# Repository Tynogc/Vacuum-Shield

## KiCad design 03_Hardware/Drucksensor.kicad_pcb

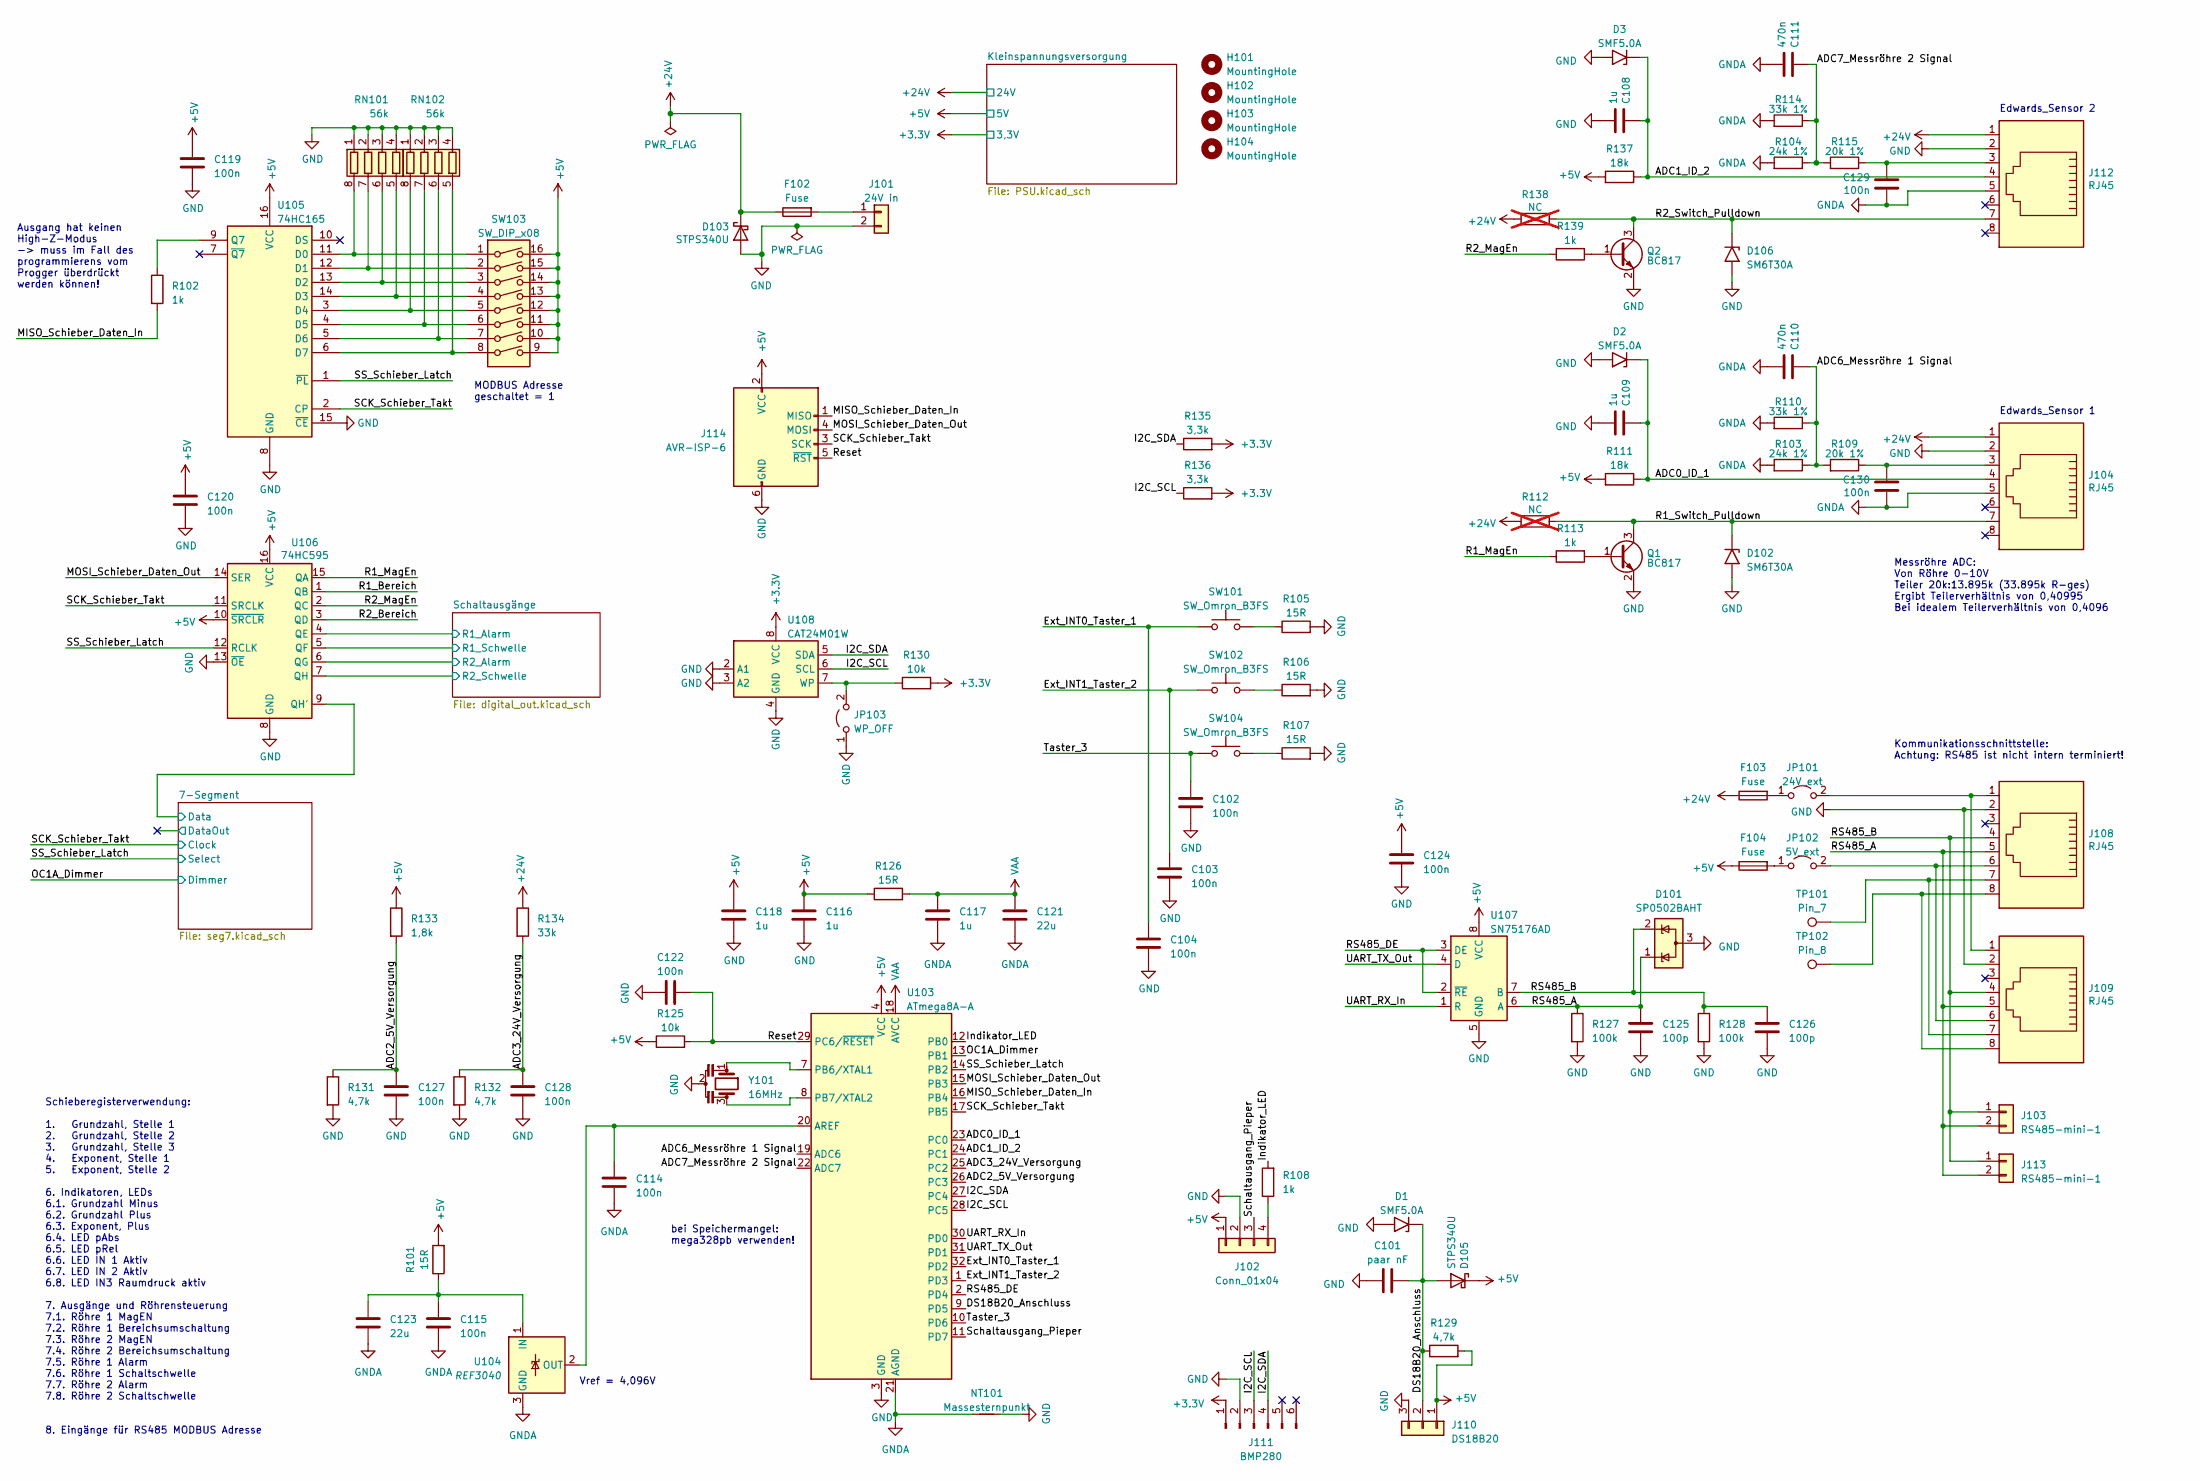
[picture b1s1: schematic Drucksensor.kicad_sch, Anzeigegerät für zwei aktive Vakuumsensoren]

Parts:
C101: paar nF; C_0603_1608Metric
C102, C103, C104, C114, C115, C119, C120, C122, C124, C127, C128, C129, C130: 100n; C_0603_1608Metric
C108, C109, C116, C117, C118: 1u; C_0603_1608Metric
C110, C111: 470n; C_0603_1608Metric
C121, C123: 22u; C_1206_3216Metric
C125, C126: 100p; C_0603_1608Metric
D1, D2, D3: SMF5.0A; D_SOD-123F
D101: SP0502BAHT; SOT-23
D102, D106: SM6T30A; D_SMB
D103, D105: STPS340U; D_SMB
F102, F103, F104: Fuse; R_1210_3225Metric
H101, H102, H103, H104: MountingHole; MountingHole_3.2mm_M3_DIN965
J101: 24V in; JST_XH_B2B-XH-A_1x02_P2.50mm_Vertical
J102: Conn_01x04; PinHeader_2x02_P2.54mm_Vertical
J103, J113: RS485-mini-1; JST_XH_B2B-XH-AM_1x02_P2.50mm_Vertical
J104, J108, J109, J112: RJ45; RJ45_Amphenol_54602_mod
J110: DS18B20; JST_XH_B3B-XH-AM_1x03_P2.50mm_Vertical
J111: BMP280; PinHeader_1x06_P2.54mm_Vertical
J114: AVR-ISP-6; IDC-Header_2x03_P2.54mm_Vertical
JP101: 24V_ext; PinHeader_1x02_P2.54mm_Vertical
JP102: 5V_ext; PinHeader_1x02_P2.54mm_Vertical
JP103: WP_OFF; PinHeader_1x02_P2.54mm_Vertical
NT101: Massesternpunkt; NetTie-2_SMD_Pad0.5mm
Q1, Q2: BC817; SOT-23
R101, R126: 15R; R_1206_3216Metric
R102, R108, R113, R139: 1k; R_0603_1608Metric
R103, R104: 24k 1%; R_0603_1608Metric
R105, R106, R107: 15R; R_0603_1608Metric
R109, R115: 20k 1%; R_0603_1608Metric
R110, R114: 33k 1%; R_0603_1608Metric
R111, R137: 18k; R_0603_1608Metric
R112, R138: NC; R_1206_3216Metric; not fitted
R125, R130: 10k; R_0603_1608Metric
R127, R128: 100k; R_0603_1608Metric
R129, R131, R132: 4,7k; R_0603_1608Metric
R133: 1,8k; R_0603_1608Metric
R134: 33k; R_0603_1608Metric
R135, R136: 3,3k; R_0603_1608Metric
RN101, RN102: 56k; R_Array_Convex_4x1206; Digikey YC164J-56KCT-ND
SW101, SW102, SW104: SW_Omron_B3FS; SW_PUSH-12mm
SW103: SW_DIP_x08; SW_DIP_SPSTx08_Slide_9.78x22.5mm_W7.62mm_P2.54mm
TP101: Pin_7; TestPoint_Keystone_5005-5009_Compact
TP102: Pin_8; TestPoint_Keystone_5005-5009_Compact
U103: ATmega8A-A; TQFP-32_7x7mm_P0.8mm
U104: REF3040; SOT-23
U105: 74HC165; SOIC-16_3.9x9.9mm_P1.27mm
U106: 74HC595; SOIC-16_3.9x9.9mm_P1.27mm
U107: SN75176AD; SOIC-8_3.9x4.9mm_P1.27mm
U108: CAT24M01W; SOIC-8_3.9x4.9mm_P1.27mm
Y101: 16MHz; Resonator_SMD_Murata_CSTxExxV-3Pin_3.0x1.1mm

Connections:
+3V3: J111.1, R130.2, R135.2, R136.2, U108.8 (VCC); also elsewhere on the board
+5V: C116.1, C118.1, C119.1, C120.1, C124.1, D105.1 (K), F104.1, J102.1, J110.1, J114.2 (VCC), R101.2, R111.2, R125.1, R126.1, R129.2, R133.1, R137.2, SW103.9, SW103.10, SW103.11, SW103.12, SW103.13, SW103.14, SW103.15, SW103.16, U103.4 (VCC), U103.6 (VCC), U105.16 (VCC), U106.10 (~SRCLR), U106.16 (VCC), U107.8 (VCC); also elsewhere on the board
+24V: D103.1 (K), F102.1, F103.1, J104.1, J112.1, R112.1, R134.1, R138.1; also elsewhere on the board
/7-Segment/Data: U106.9 (QH'); also elsewhere on the board
/ADC0_ID_1: C109.1, D2.1 (A1), J104.4, R111.1, U103.23 (PC0)
/ADC1_ID_2: C108.1, D3.1 (A1), J112.4, R137.1, U103.24 (PC1)
/ADC2_5V_Versorgung: C127.1, R131.1, R133.2, U103.26 (PC3)
/ADC3_24V_Versorgung: C128.1, R132.1, R134.2, U103.25 (PC2)
/ADC6_Messröhre 1 Signal: C110.1, R103.1, R109.2, R110.1, U103.19 (ADC6)
/ADC7_Messröhre 2 Signal: C111.1, R104.1, R114.1, R115.2, U103.22 (ADC7)
/DS18B20_Anschluss: C101.2, D1.1 (A1), D105.2 (A), J110.2, R129.1, U103.9 (PD5)
/Ext_INT0_Taster_1: C104.1, SW101.1, U103.32 (PD2)
/Ext_INT1_Taster_2: C103.1, SW102.1, U103.1 (PD3)
/I2C_SCL: J111.3, R136.1, U103.28 (PC5), U108.6 (SCL)
/I2C_SDA: J111.4, R135.1, U103.27 (PC4), U108.5 (SDA)
/Indikator_LED: R108.2, U103.12 (PB0)
/MISO_Schieber_Daten_In: J114.1 (MISO), R102.2, U103.16 (PB4)
/MOSI_Schieber_Daten_Out: J114.4 (MOSI), U103.15 (PB3), U106.14 (SER)
/OC1A_Dimmer: U103.13 (PB1); also elsewhere on the board
/R1_Bereich: U106.1 (QB)
/R1_MagEn: R113.1, U106.15 (QA)
/R1_Switch_Pulldown: D102.1 (A1), J104.7, Q1.3 (C), R112.2
/R2_Bereich: U106.3 (QD)
/R2_MagEn: R139.1, U106.2 (QC)
/R2_Switch_Pulldown: D106.1 (A1), J112.7, Q2.3 (C), R138.2
/RS485_A: C125.1, D101.1 (K), J103.2, J108.5, J109.5, J113.2, R127.1, U107.6 (A)
/RS485_B: C126.1, D101.2 (K), J103.1, J108.4, J109.4, J113.1, R128.1, U107.7 (B)
/RS485_DE: U103.2 (PD4), U107.2 (~RE), U107.3 (DE)
/Reset: C122.2, J114.5 (~RST), R125.2, U103.29 (PC6/~RESET)
/SCK_Schieber_Takt: J114.3 (SCK), U103.17 (PB5), U105.2 (CP), U106.11 (SRCLK); also elsewhere on the board
/SS_Schieber_Latch: U103.14 (PB2), U105.1 (~PL), U106.12 (RCLK); also elsewhere on the board
/Schaltausgang_Pieper: J102.3, U103.11 (PD7)
/Schaltausgänge/R1_Alarm: U106.4 (QE); also elsewhere on the board
/Schaltausgänge/R1_Schwelle: U106.5 (QF); also elsewhere on the board
/Schaltausgänge/R2_Alarm: U106.6 (QG); also elsewhere on the board
/Schaltausgänge/R2_Schwelle: U106.7 (QH); also elsewhere on the board
/Taster_3: C102.1, SW104.1, U103.10 (PD6)
/UART_RX_In: U103.30 (PD0), U107.1 (R)
/UART_TX_Out: U103.31 (PD1), U107.4 (D)
GND: C101.1, C102.2, C103.2, C104.2, C108.2, C109.2, C116.2, C118.2, C119.2, C120.2, C122.1, C124.2, C125.2, C126.2, C127.2, C128.2, D1.2 (A2), D2.2 (A2), D3.2 (A2), D101.3 (A), D102.2 (A2), D103.2 (A), D106.2 (A2), J101.2, J102.2, J104.2, J108.2, J109.2, J110.3, J111.2, J112.2, J114.6 (GND), JP103.1 (A), NT101.2, Q1.2 (E), Q2.2 (E), R105.2, R106.2, R107.2, R127.2, R128.2, R131.2, R132.2, RN101.1 (R1.1), RN101.2 (R2.1), RN101.3 (R3.1), RN101.4 (R4.1), RN102.1 (R1.1), RN102.2 (R2.1), RN102.3 (R3.1), RN102.4 (R4.1), U103.3 (GND), U103.5 (GND), U105.8 (GND), U105.15 (~CE), U106.8 (GND), U106.13 (~OE), U107.5 (GND), U108.2 (A1), U108.3 (A2), U108.4 (GND), Y101.2; also elsewhere on the board
GNDA: C110.2, C111.2, C114.2, C115.2, C117.2, C121.2, C123.2, C129.2, C130.2, J104.5, J112.5, NT101.1, R103.2, R104.2, R110.2, R114.2, U103.21 (AGND), U104.3 (GND)
unnamed: C129.1, J112.3, R115.1
unnamed: C130.1, J104.3, R109.1
unnamed: F102.2, J101.1
unnamed: J102.4, R108.1
unnamed: J108.7, J109.7, TP101.1
unnamed: J108.8, J109.8, TP102.1
unnamed: F103.2, JP101.1 (A)
unnamed: J108.1, J109.1, JP101.2 (B)
unnamed: F104.2, JP102.1 (A)
unnamed: J108.6, J109.6, JP102.2 (B)
unnamed: JP103.2 (B), R130.1, U108.7 (WP)
unnamed: Q1.1 (B), R113.2
unnamed: Q2.1 (B), R139.2
unnamed: R105.1, SW101.2
unnamed: R106.1, SW102.2
unnamed: R107.1, SW104.2
unnamed: RN101.8 (R1.2), SW103.1, U105.11 (D0)
unnamed: RN101.7 (R2.2), SW103.2, U105.12 (D1)
unnamed: RN101.6 (R3.2), SW103.3, U105.13 (D2)
unnamed: RN101.5 (R4.2), SW103.4, U105.14 (D3)
unnamed: RN102.8 (R1.2), SW103.5, U105.3 (D4)
unnamed: RN102.7 (R2.2), SW103.6, U105.4 (D5)
unnamed: RN102.6 (R3.2), SW103.7, U105.5 (D6)
unnamed: RN102.5 (R4.2), SW103.8, U105.6 (D7)
unnamed: C114.1, U103.20 (AREF), U104.2 (OUT)
unnamed: U103.7 (PB6/XTAL1), Y101.1
unnamed: U103.8 (PB7/XTAL2), Y101.3
unnamed: C115.1, C123.1, R101.1, U104.1 (IN)
unnamed: R102.1, U105.9 (Q7)
VAA: C117.1, C121.1, R126.2, U103.18 (AVCC)

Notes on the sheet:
Messröhre ADC: Von Röhre 0-10V Teiler 20k:13.895k (33.895k R-ges) Ergibt Teilerverhältnis von 0,40995 Bei idealem Teilerverhältnis von 0,4096
MODBUS Adresse geschaltet = 1
Edwards_Sensor 2
bei Speichermangel: mega328pb verwenden!
Edwards_Sensor 1
Kommunikationsschnittstelle: Achtung: RS485 ist nicht intern terminiert!
Ausgang hat keinen High-Z-Modus -> muss im Fall des programmierens vom Progger überdrückt werden können!
Schieberegisterverwendung: 1. Grundzahl, Stelle 1 2. Grundzahl, Stelle 2 3. Grundzahl, Stelle 3 4. Exponent, Stelle 1 5. Exponent, Stelle 2 6. Indikatoren, LEDs 6.1. Grundzahl Minus 6.2. Grundzahl Plus 6.3. Exponent, Plus 6.4. LED pAbs 6.5. LED pRel 6.6. LED IN 1 Aktiv 6.7. LED IN 2 Aktiv 6.8. LED 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
Vref = 4,096V

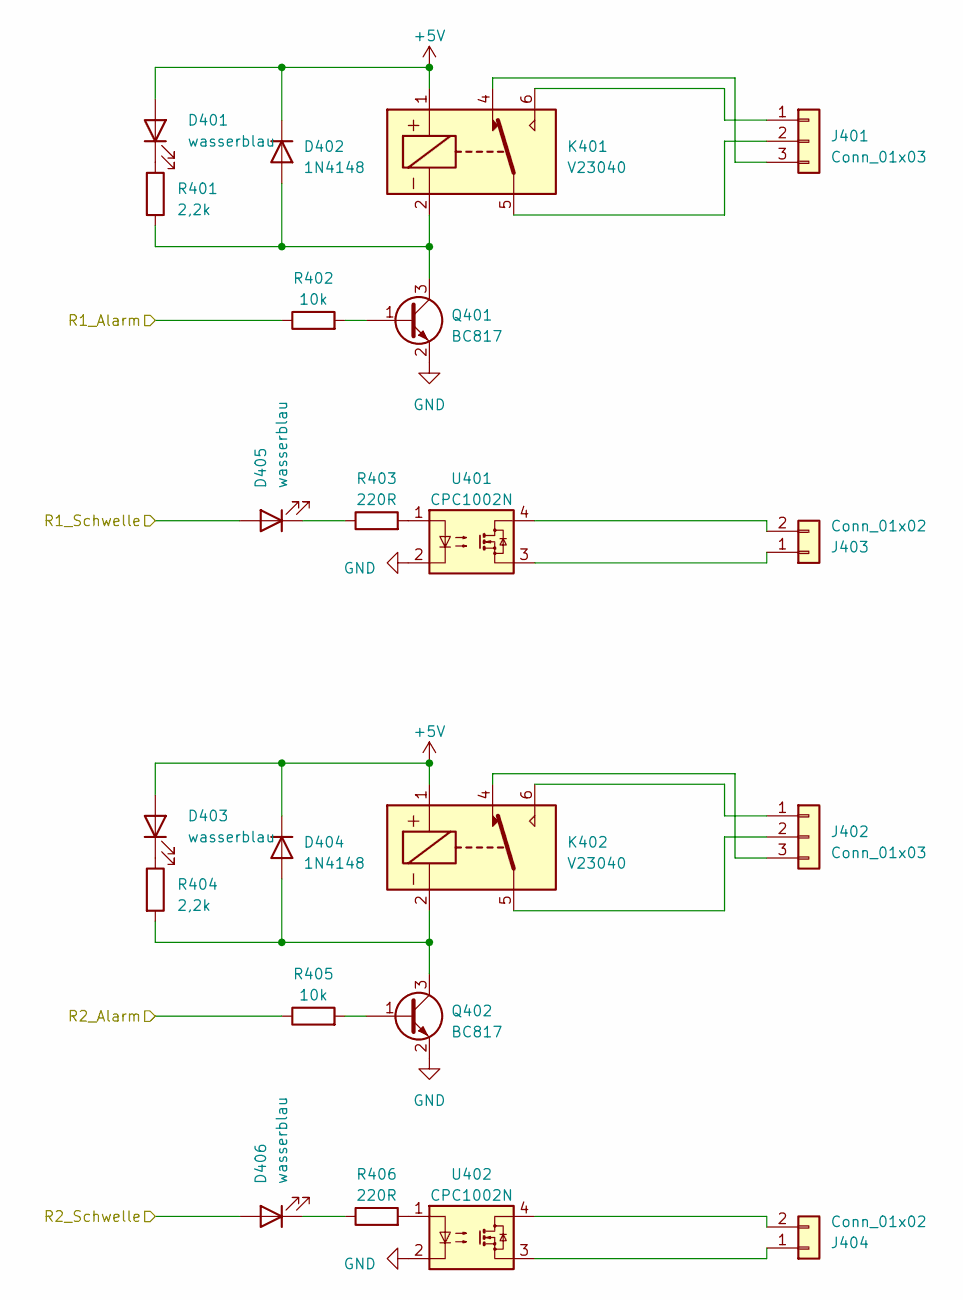
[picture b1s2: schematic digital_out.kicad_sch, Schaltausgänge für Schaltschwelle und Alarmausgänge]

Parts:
D401, D403, D405, D406: wasserblau; LED_0603_1608Metric
D402, D404: 1N4148; D_MiniMELF
J401, J402: Conn_01x03; Wago_734-133_1x03_P3.50mm_Vertical
J403, J404: Conn_01x02; Wago_734-132_1x02_P3.50mm_Vertical
K401, K402: V23040
Q401, Q402: BC817; SOT-23
R401, R404: 2,2k; R_0603_1608Metric
R402, R405: 10k; R_0603_1608Metric
R403, R406: 220R; R_0603_1608Metric
U401, U402: CPC1002N; SOP-4_3.8x4.1mm_P2.54mm

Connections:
+5V: D401.2 (A), D402.1 (K), D403.2 (A), D404.1 (K), K401.1, K402.1; also elsewhere on the board
/Schaltausgänge/R1_Alarm: R402.1; also elsewhere on the board
/Schaltausgänge/R1_Schwelle: D405.2 (A); also elsewhere on the board
/Schaltausgänge/R2_Alarm: R405.1; also elsewhere on the board
/Schaltausgänge/R2_Schwelle: D406.2 (A); also elsewhere on the board
GND: Q401.2 (E), Q402.2 (E), U401.2, U402.2; also elsewhere on the board
unnamed: D401.1 (K), R401.1
unnamed: D402.2 (A), K401.2, Q401.3 (C), R401.2
unnamed: D403.1 (K), R404.1
unnamed: D404.2 (A), K402.2, Q402.3 (C), R404.2
unnamed: D405.1 (K), R403.1
unnamed: D406.1 (K), R406.1
unnamed: J401.1, K401.6
unnamed: J401.2, K401.5
unnamed: J401.3, K401.4
unnamed: J402.1, K402.6
unnamed: J402.2, K402.5
unnamed: J402.3, K402.4
unnamed: J403.1, U401.3
unnamed: J403.2, U401.4
unnamed: J404.1, U402.3
unnamed: J404.2, U402.4
unnamed: Q401.1 (B), R402.2
unnamed: Q402.1 (B), R405.2
unnamed: R403.2, U401.1
unnamed: R406.2, U402.1

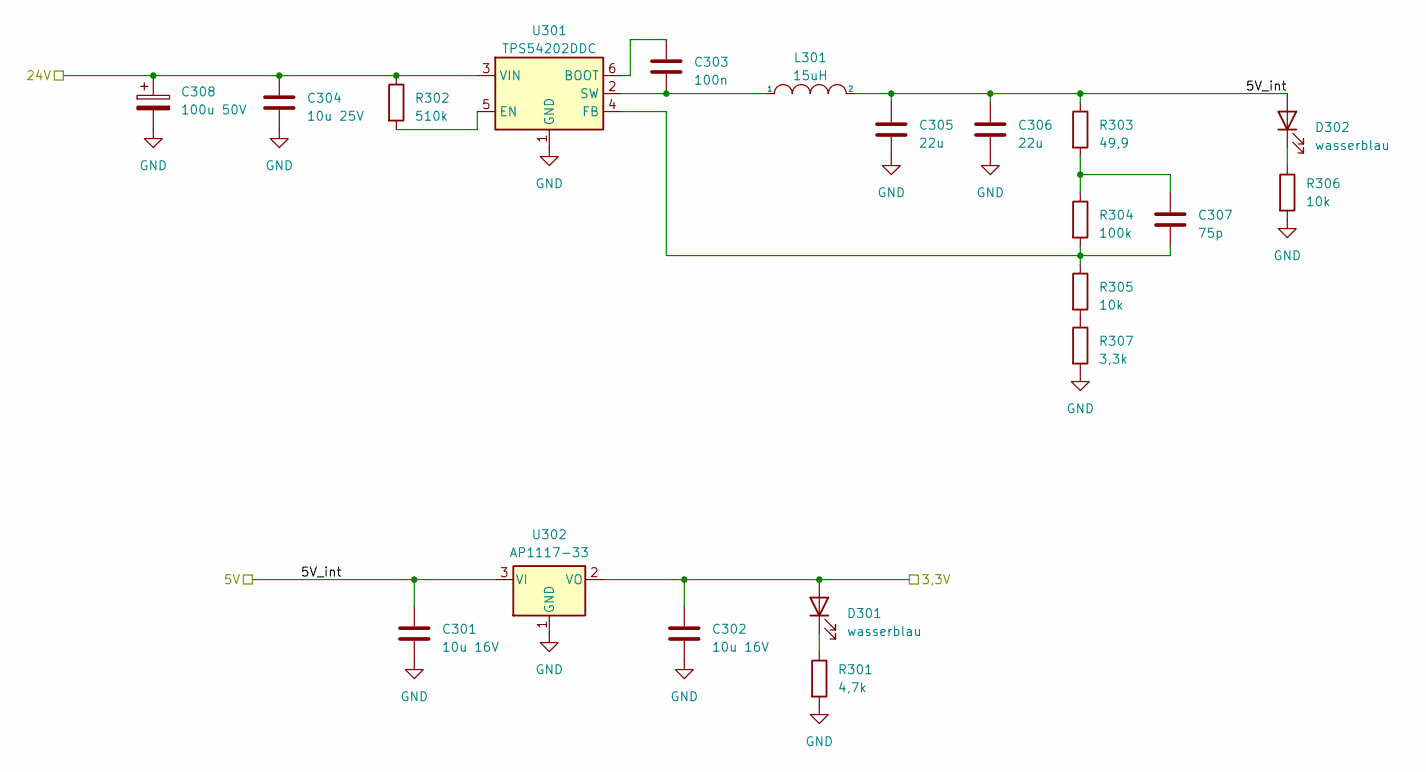
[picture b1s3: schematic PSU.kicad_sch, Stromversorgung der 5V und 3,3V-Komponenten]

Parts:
C301, C302: 10u 16V; C_1206_3216Metric
C303: 100n; C_0603_1608Metric
C304: 10u 25V; C_1206_3216Metric
C305, C306: 22u; C_1206_3216Metric
C307: 75p; C_0603_1608Metric
C308: 100u 50V; CP_Radial_D8.0mm_P3.50mm
D301, D302: wasserblau; LED_0603_1608Metric
L301: 15uH; L_Bourns-SRN4018
R301: 4,7k; R_0603_1608Metric
R302: 510k; R_0603_1608Metric
R303: 49,9; R_0603_1608Metric
R304: 100k; R_0603_1608Metric
R305, R306: 10k; R_0603_1608Metric
R307: 3,3k; R_0603_1608Metric
U301: TPS54202DDC; SOT-23-6
U302: AP1117-33; SOT-223-3_TabPin2

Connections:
+3V3: C302.1, D301.2 (A), U302.2 (VO); also elsewhere on the board
+5V: C301.1, C305.1, C306.1, D302.2 (A), L301.2, R303.1, U302.3 (VI); also elsewhere on the board
+24V: C304.1, C308.1, R302.1, U301.3 (VIN); also elsewhere on the board
GND: C301.2, C302.2, C304.2, C305.2, C306.2, C308.2, R301.2, R306.2, R307.2, U301.1 (GND), U302.1 (GND); also elsewhere on the board
unnamed: C307.1, R303.2, R304.1
unnamed: D301.1 (K), R301.1
unnamed: D302.1 (K), R306.1
unnamed: R305.2, R307.1
unnamed: C303.1, U301.6 (BOOT)
unnamed: R302.2, U301.5 (EN)
unnamed: C307.2, R304.2, R305.1, U301.4 (FB)
unnamed: C303.2, L301.1, U301.2 (SW)

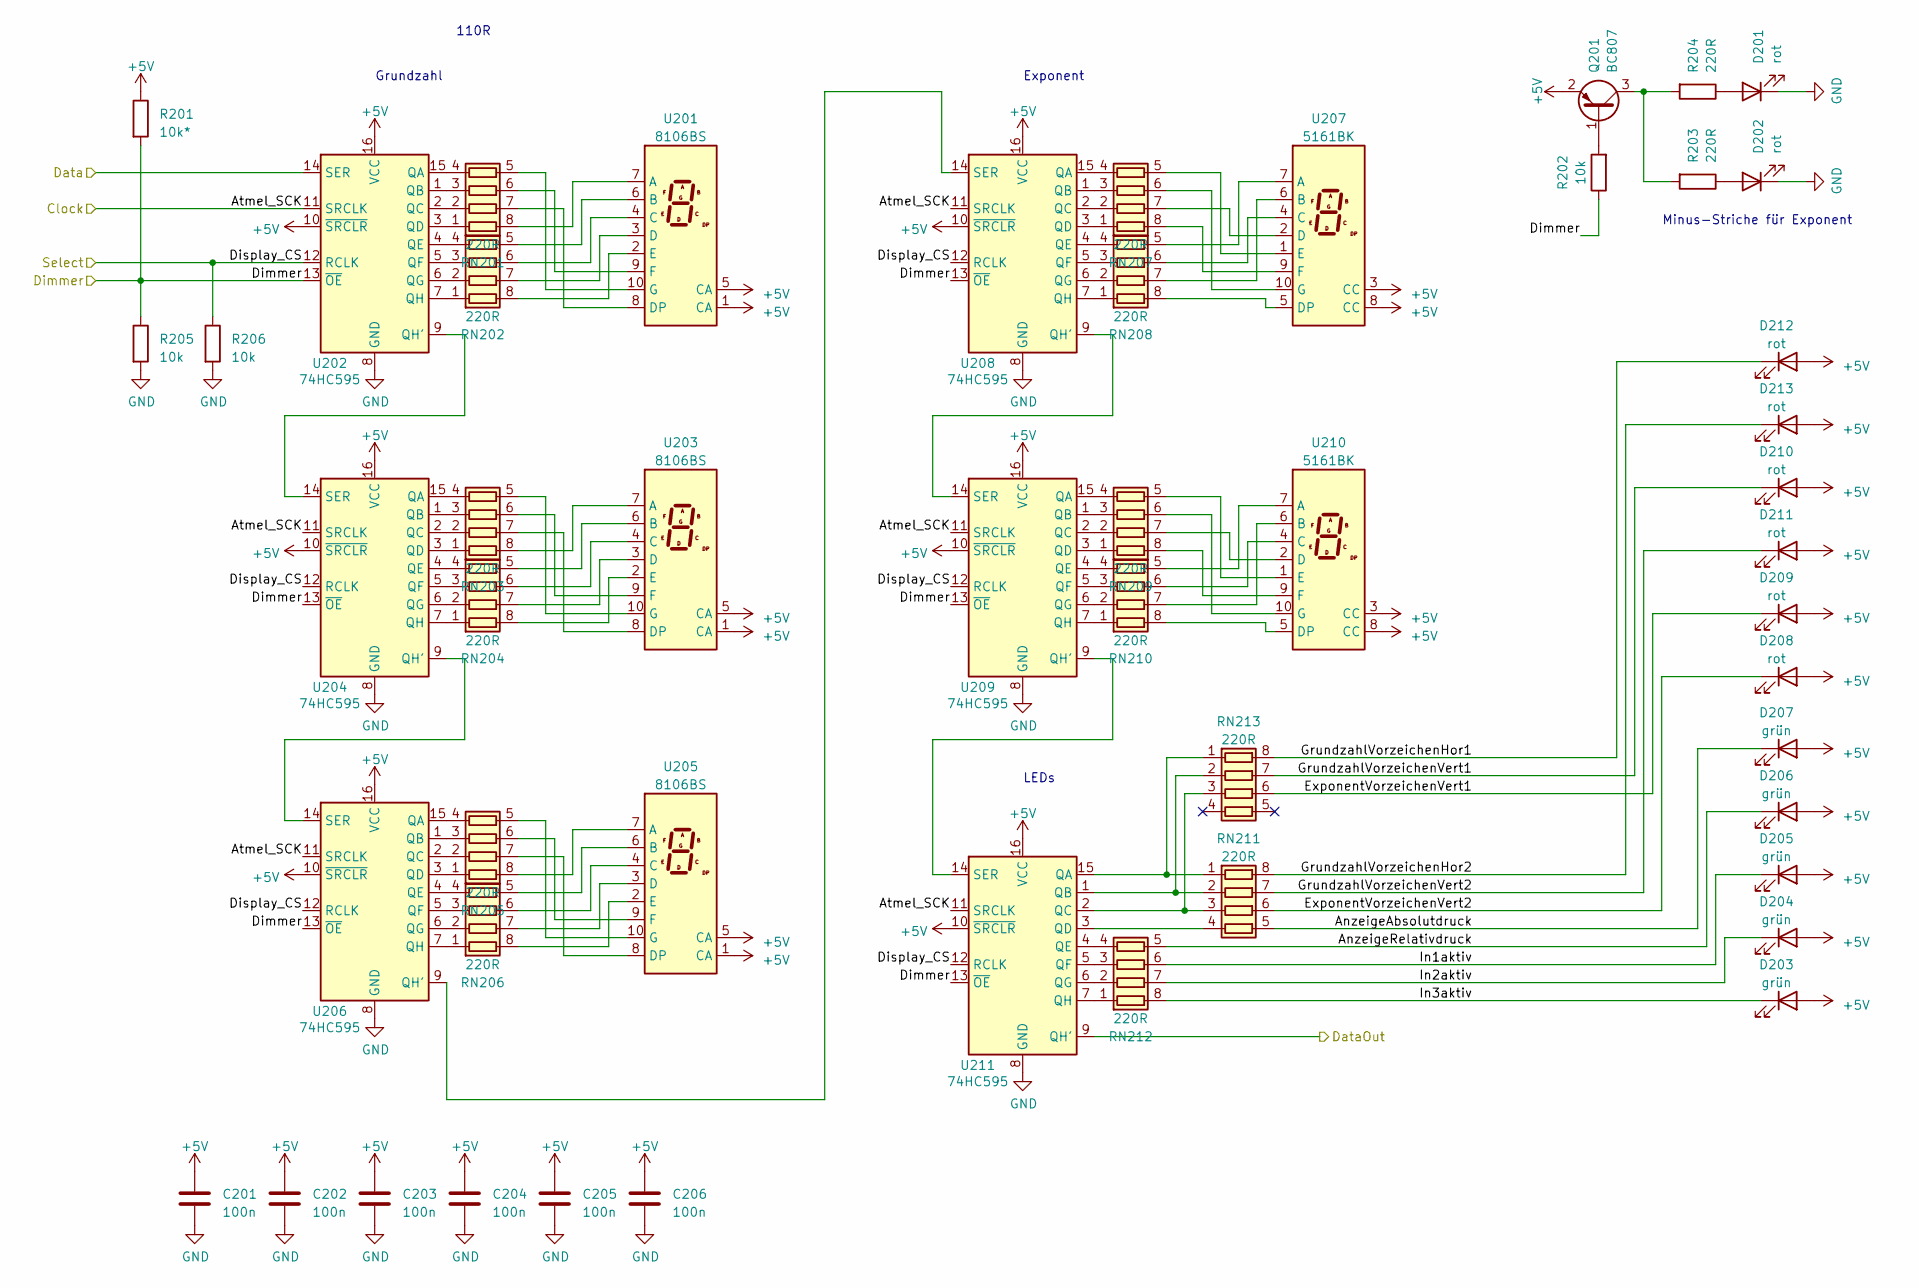
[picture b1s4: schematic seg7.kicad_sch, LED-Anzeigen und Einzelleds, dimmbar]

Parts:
C201, C202, C203, C204, C205, C206: 100n; C_0603_1608Metric
D201, D202, D208, D209, D210, D211, D212, D213: rot; LED_Rectangular_W3.0mm_H2.0mm
D203, D204, D205, D206, D207: grün; LED_D5.0mm
Q201: BC807; SOT-23
R201: 10k*; R_0603_1608Metric
R202, R205, R206: 10k; R_0603_1608Metric
R203, R204: 220R; R_0603_1608Metric
RN201, RN202, RN203, RN204, RN205, RN206, RN207, RN208, RN209, RN210, RN211, RN212, RN213: 220R; R_Array_Convex_4x1206; Digikey YC164J-220CT-ND
U201, U203, U205: 8106BS
U202, U204, U206, U208, U209, U211: 74HC595; SOIC-16_3.9x9.9mm_P1.27mm
U207, U210: 5161BK; D1X8K

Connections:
+5V: C201.1, C202.1, C203.1, C204.1, C205.1, C206.1, D203.2 (A), D204.2 (A), D205.2 (A), D206.2 (A), D207.2 (A), D208.2 (A), D209.2 (A), D210.2 (A), D211.2 (A), D212.2 (A), D213.2 (A), Q201.2 (E), R201.1, U201.1 (CA), U201.5 (CA), U202.10 (~SRCLR), U202.16 (VCC), U203.1 (CA), U203.5 (CA), U204.10 (~SRCLR), U204.16 (VCC), U205.1 (CA), U205.5 (CA), U206.10 (~SRCLR), U206.16 (VCC), U207.3 (CC), U207.8 (CC), U208.10 (~SRCLR), U208.16 (VCC), U209.10 (~SRCLR), U209.16 (VCC), U210.3 (CC), U210.8 (CC), U211.10 (~SRCLR), U211.16 (VCC); also elsewhere on the board
/7-Segment/AnzeigeAbsolutdruck: D207.1 (K), RN211.5 (R4.2)
/7-Segment/AnzeigeRelativdruck: D206.1 (K), RN212.5 (R4.2)
/7-Segment/Data: U202.14 (SER); also elsewhere on the board
/7-Segment/DataOut: U211.9 (QH')
/7-Segment/ExponentVorzeichenVert1: D209.1 (K), RN213.6 (R3.2)
/7-Segment/ExponentVorzeichenVert2: D208.1 (K), RN211.6 (R3.2)
/7-Segment/GrundzahlVorzeichenHor1: D212.1 (K), RN213.8 (R1.2)
/7-Segment/GrundzahlVorzeichenHor2: D213.1 (K), RN211.8 (R1.2)
/7-Segment/GrundzahlVorzeichenVert1: D210.1 (K), RN213.7 (R2.2)
/7-Segment/GrundzahlVorzeichenVert2: D211.1 (K), RN211.7 (R2.2)
/7-Segment/In1aktiv: D205.1 (K), RN212.6 (R3.2)
/7-Segment/In2aktiv: D204.1 (K), RN212.7 (R2.2)
/7-Segment/In3aktiv: D203.1 (K), RN212.8 (R1.2)
/OC1A_Dimmer: R201.2, R202.1, R205.1, U202.13 (~OE), U204.13 (~OE), U206.13 (~OE), U208.13 (~OE), U209.13 (~OE), U211.13 (~OE); also elsewhere on the board
/SCK_Schieber_Takt: U202.11 (SRCLK), U204.11 (SRCLK), U206.11 (SRCLK), U208.11 (SRCLK), U209.11 (SRCLK), U211.11 (SRCLK); also elsewhere on the board
/SS_Schieber_Latch: R206.1, U202.12 (RCLK), U204.12 (RCLK), U206.12 (RCLK), U208.12 (RCLK), U209.12 (RCLK), U211.12 (RCLK); also elsewhere on the board
GND: C201.2, C202.2, C203.2, C204.2, C205.2, C206.2, D201.1 (K), D202.1 (K), R205.2, R206.2, U202.8 (GND), U204.8 (GND), U206.8 (GND), U208.8 (GND), U209.8 (GND), U211.8 (GND); also elsewhere on the board
unnamed: D201.2 (A), R204.1
unnamed: D202.2 (A), R203.1
unnamed: Q201.1 (B), R202.2
unnamed: Q201.3 (C), R203.2, R204.2
unnamed: RN201.1 (R1.1), U202.3 (QD)
unnamed: RN201.8 (R1.2), U201.7 (A)
unnamed: RN201.2 (R2.1), U202.2 (QC)
unnamed: RN201.7 (R2.2), U201.8 (DP)
unnamed: RN201.3 (R3.1), U202.1 (QB)
unnamed: RN201.6 (R3.2), U201.9 (F)
unnamed: RN201.4 (R4.1), U202.15 (QA)
unnamed: RN201.5 (R4.2), U201.10 (G)
unnamed: RN202.1 (R1.1), U202.7 (QH)
unnamed: RN202.8 (R1.2), U201.2 (E)
unnamed: RN202.2 (R2.1), U202.6 (QG)
unnamed: RN202.7 (R2.2), U201.3 (D)
unnamed: RN202.3 (R3.1), U202.5 (QF)
unnamed: RN202.6 (R3.2), U201.4 (C)
unnamed: RN202.4 (R4.1), U202.4 (QE)
unnamed: RN202.5 (R4.2), U201.6 (B)
unnamed: RN203.1 (R1.1), U204.3 (QD)
unnamed: RN203.8 (R1.2), U203.7 (A)
unnamed: RN203.2 (R2.1), U204.2 (QC)
unnamed: RN203.7 (R2.2), U203.8 (DP)
unnamed: RN203.3 (R3.1), U204.1 (QB)
unnamed: RN203.6 (R3.2), U203.9 (F)
unnamed: RN203.4 (R4.1), U204.15 (QA)
unnamed: RN203.5 (R4.2), U203.10 (G)
unnamed: RN204.1 (R1.1), U204.7 (QH)
unnamed: RN204.8 (R1.2), U203.2 (E)
unnamed: RN204.2 (R2.1), U204.6 (QG)
unnamed: RN204.7 (R2.2), U203.3 (D)
unnamed: RN204.3 (R3.1), U204.5 (QF)
unnamed: RN204.6 (R3.2), U203.4 (C)
unnamed: RN204.4 (R4.1), U204.4 (QE)
unnamed: RN204.5 (R4.2), U203.6 (B)
unnamed: RN205.1 (R1.1), U206.3 (QD)
unnamed: RN205.8 (R1.2), U205.7 (A)
unnamed: RN205.2 (R2.1), U206.2 (QC)
unnamed: RN205.7 (R2.2), U205.8 (DP)
unnamed: RN205.3 (R3.1), U206.1 (QB)
unnamed: RN205.6 (R3.2), U205.9 (F)
unnamed: RN205.4 (R4.1), U206.15 (QA)
unnamed: RN205.5 (R4.2), U205.10 (G)
unnamed: RN206.1 (R1.1), U206.7 (QH)
unnamed: RN206.8 (R1.2), U205.2 (E)
unnamed: RN206.2 (R2.1), U206.6 (QG)
unnamed: RN206.7 (R2.2), U205.3 (D)
unnamed: RN206.3 (R3.1), U206.5 (QF)
unnamed: RN206.6 (R3.2), U205.4 (C)
unnamed: RN206.4 (R4.1), U206.4 (QE)
unnamed: RN206.5 (R4.2), U205.6 (B)
unnamed: RN207.1 (R1.1), U208.3 (QD)
unnamed: RN207.8 (R1.2), U207.9 (F)
unnamed: RN207.2 (R2.1), U208.2 (QC)
unnamed: RN207.7 (R2.2), U207.2 (D)
unnamed: RN207.3 (R3.1), U208.1 (QB)
unnamed: RN207.6 (R3.2), U207.10 (G)
unnamed: RN207.4 (R4.1), U208.15 (QA)
unnamed: RN207.5 (R4.2), U207.1 (E)
unnamed: RN208.1 (R1.1), U208.7 (QH)
unnamed: RN208.8 (R1.2), U207.5 (DP)
unnamed: RN208.2 (R2.1), U208.6 (QG)
unnamed: RN208.7 (R2.2), U207.6 (B)
unnamed: RN208.3 (R3.1), U208.5 (QF)
unnamed: RN208.6 (R3.2), U207.4 (C)
unnamed: RN208.4 (R4.1), U208.4 (QE)
unnamed: RN208.5 (R4.2), U207.7 (A)
unnamed: RN209.1 (R1.1), U209.3 (QD)
unnamed: RN209.8 (R1.2), U210.9 (F)
unnamed: RN209.2 (R2.1), U209.2 (QC)
unnamed: RN209.7 (R2.2), U210.2 (D)
unnamed: RN209.3 (R3.1), U209.1 (QB)
unnamed: RN209.6 (R3.2), U210.10 (G)
unnamed: RN209.4 (R4.1), U209.15 (QA)
unnamed: RN209.5 (R4.2), U210.1 (E)
unnamed: RN210.1 (R1.1), U209.7 (QH)
unnamed: RN210.8 (R1.2), U210.5 (DP)
unnamed: RN210.2 (R2.1), U209.6 (QG)
unnamed: RN210.7 (R2.2), U210.6 (B)
unnamed: RN210.3 (R3.1), U209.5 (QF)
unnamed: RN210.6 (R3.2), U210.4 (C)
unnamed: RN210.4 (R4.1), U209.4 (QE)
unnamed: RN210.5 (R4.2), U210.7 (A)
unnamed: RN211.1 (R1.1), RN213.1 (R1.1), U211.15 (QA)
unnamed: RN211.2 (R2.1), RN213.2 (R2.1), U211.1 (QB)
unnamed: RN211.3 (R3.1), RN213.3 (R3.1), U211.2 (QC)
unnamed: RN211.4 (R4.1), U211.3 (QD)
unnamed: RN212.1 (R1.1), U211.7 (QH)
unnamed: RN212.2 (R2.1), U211.6 (QG)
unnamed: RN212.3 (R3.1), U211.5 (QF)
unnamed: RN212.4 (R4.1), U211.4 (QE)
unnamed: U202.9 (QH'), U204.14 (SER)
unnamed: U204.9 (QH'), U206.14 (SER)
unnamed: U206.9 (QH'), U208.14 (SER)
unnamed: U208.9 (QH'), U209.14 (SER)
unnamed: U209.9 (QH'), U211.14 (SER)

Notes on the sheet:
Exponent
Minus-Striche für Exponent
110R
LEDs
Grundzahl

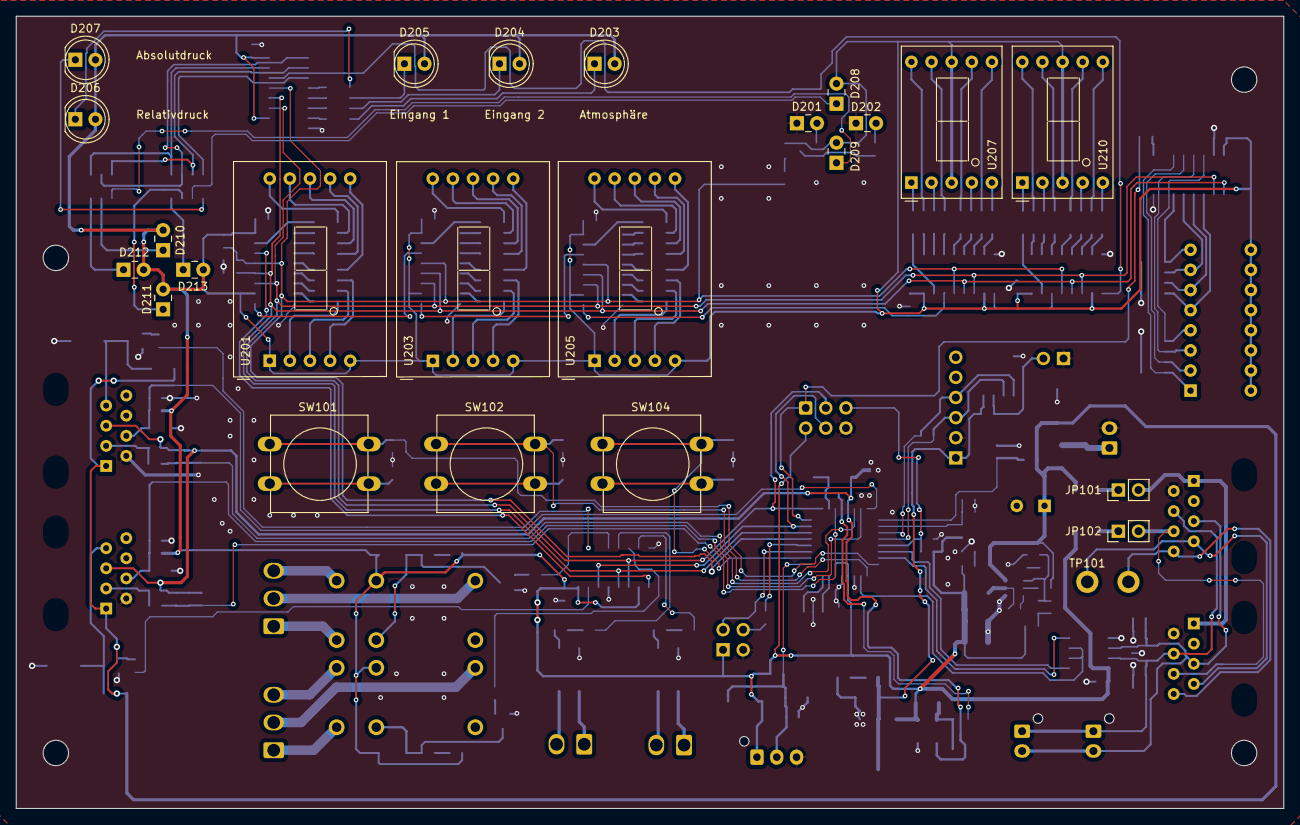
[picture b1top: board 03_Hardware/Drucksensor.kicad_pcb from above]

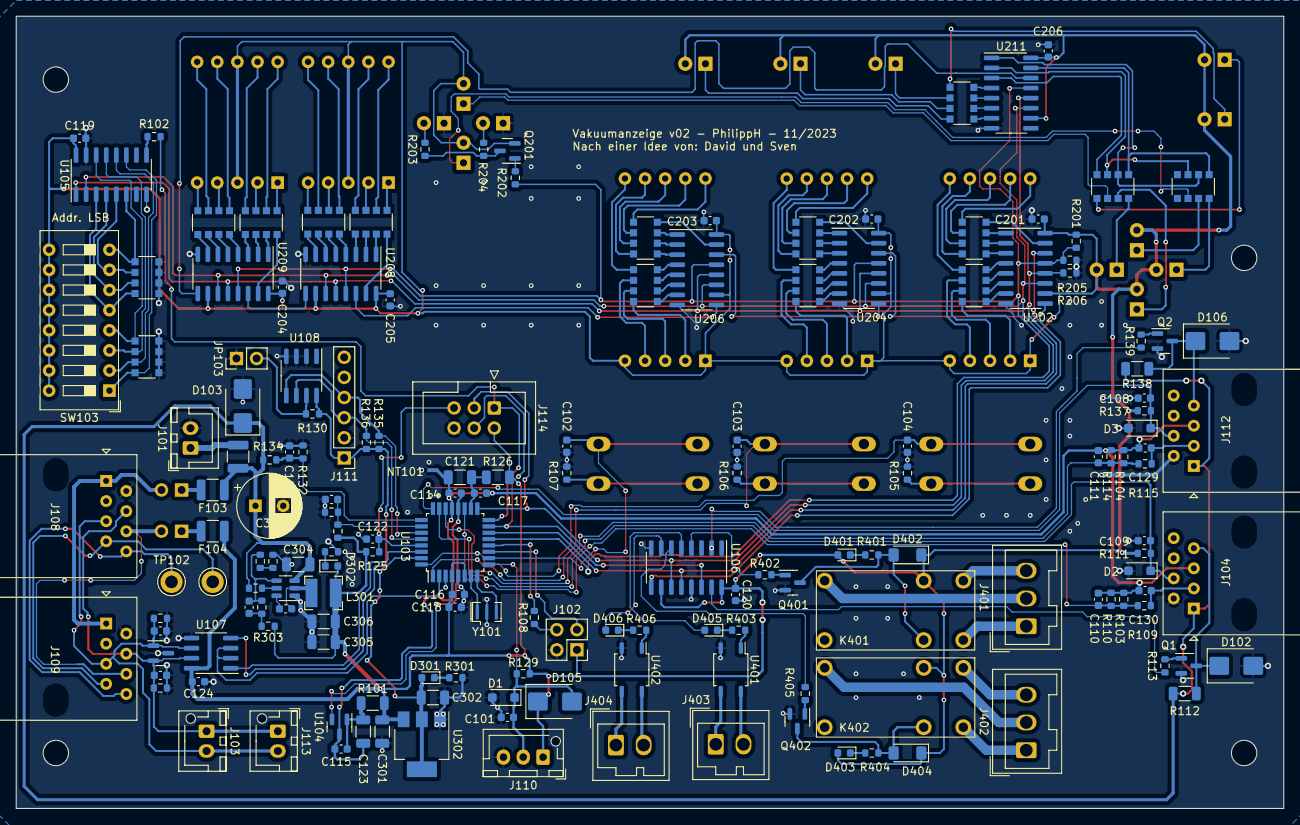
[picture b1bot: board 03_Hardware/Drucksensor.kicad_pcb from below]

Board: 2 copper layers, 160.0 x 100.0 mm, 194 parts (167 on the bottom side), 205 nets.
